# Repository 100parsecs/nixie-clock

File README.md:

# nixie-clock
This is a design for a nixie tube clock that runs exclusively on transistor logic.

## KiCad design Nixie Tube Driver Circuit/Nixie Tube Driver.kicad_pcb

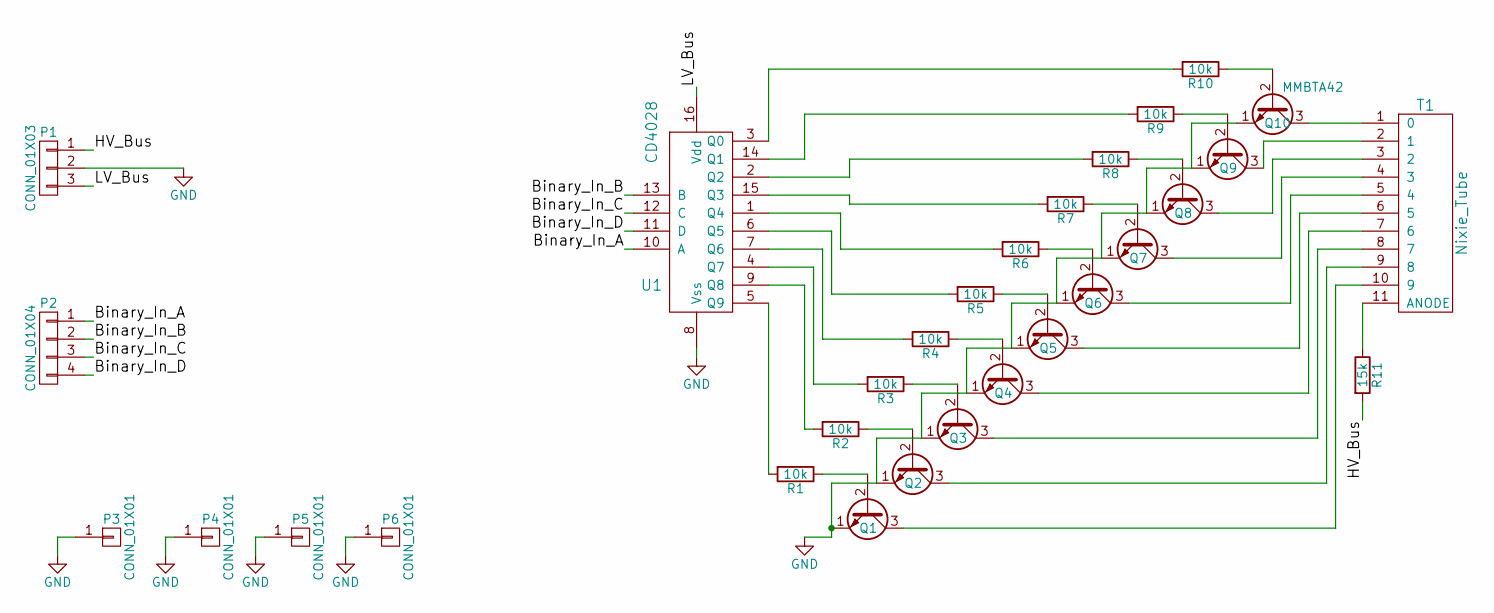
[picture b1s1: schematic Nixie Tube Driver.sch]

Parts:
P1: CONN_01X03; Molex_Microfit3_Header_02x02_Straight_43045-0428
P2: CONN_01X04; Molex_Microfit3_Header_02x02_Straight_43045-0428
P3, P4, P5, P6: CONN_01X01; MountingHole_2.5mm_Pad
Q1, Q2, Q3, Q4, Q5, Q6, Q7, Q8, Q9, Q10: MMBTA42; SOT-23_Handsoldering
R1, R2, R3, R4, R5, R6, R7, R8, R9, R10: 10k; R_0805_HandSoldering
R11: 15k; R_1218_HandSoldering
T1: Nixie_Tube; IN12B_Discrete_Pins_Keyed_Measured_Pos
U1: CD4028; SOIC-16_3.9x9.9mm_Pitch1.27mm

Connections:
/Binary_In_A: P2.1, U1.10 (A)
/Binary_In_B: P2.2, U1.13 (B)
/Binary_In_C: P2.3, U1.12 (C)
/Binary_In_D: P2.4, U1.11 (D)
/HV_Bus: P1.1, R11.2
/LV_Bus: P1.3, U1.16 (Vdd)
GND: P1.2, P3.1, P4.1, P5.1, P6.1, Q1.1 (E), Q2.1 (E), Q3.1 (E), Q4.1 (E), Q5.1 (E), Q6.1 (E), Q7.1 (E), Q8.1 (E), Q9.1 (E), Q10.1 (E), U1.8 (Vss)
unnamed: Q1.2 (B), R1.1
unnamed: Q1.3 (C), T1.10 (9)
unnamed: Q2.2 (B), R2.1
unnamed: Q2.3 (C), T1.9 (8)
unnamed: Q3.2 (B), R3.1
unnamed: Q3.3 (C), T1.8 (7)
unnamed: Q4.2 (B), R4.1
unnamed: Q4.3 (C), T1.7 (6)
unnamed: Q5.2 (B), R5.1
unnamed: Q5.3 (C), T1.6 (5)
unnamed: Q6.2 (B), R6.1
unnamed: Q6.3 (C), T1.5 (4)
unnamed: Q7.2 (B), R7.1
unnamed: Q7.3 (C), T1.4 (3)
unnamed: Q8.2 (B), R8.1
unnamed: Q8.3 (C), T1.3 (2)
unnamed: Q9.2 (B), R9.1
unnamed: Q9.3 (C), T1.2 (1)
unnamed: Q10.2 (B), R10.1
unnamed: Q10.3 (C), T1.1 (0)
unnamed: R1.2, U1.5 (Q9)
unnamed: R2.2, U1.9 (Q8)
unnamed: R3.2, U1.4 (Q7)
unnamed: R4.2, U1.7 (Q6)
unnamed: R5.2, U1.6 (Q5)
unnamed: R6.2, U1.1 (Q4)
unnamed: R7.2, U1.15 (Q3)
unnamed: R8.2, U1.2 (Q2)
unnamed: R9.2, U1.14 (Q1)
unnamed: R10.2, U1.3 (Q0)
unnamed: R11.1, T1.11 (ANODE)

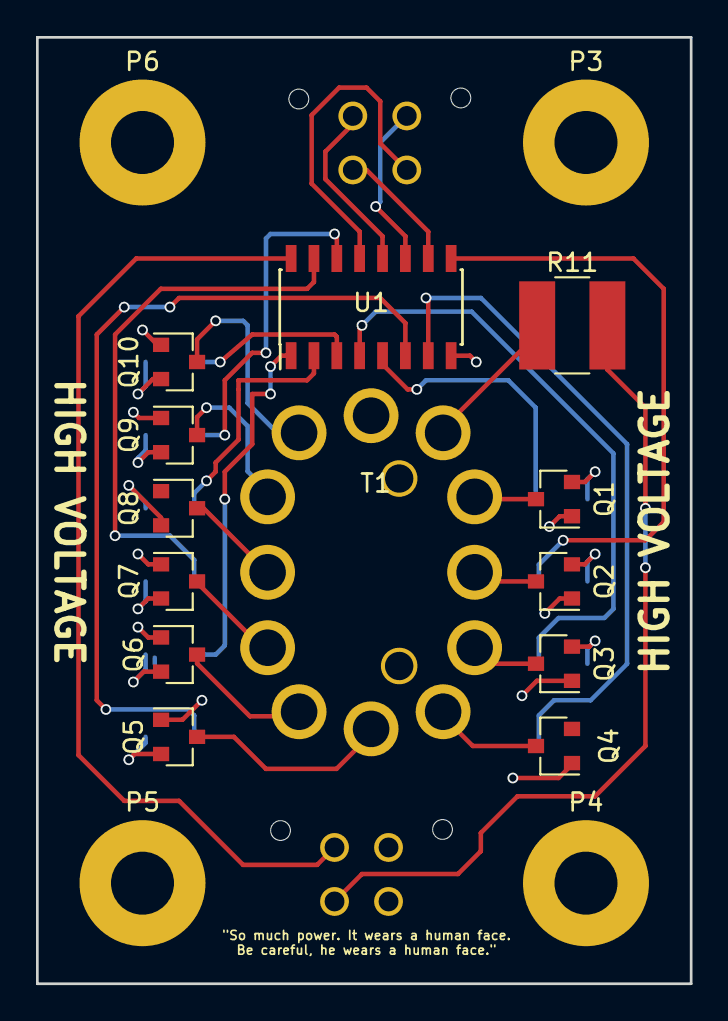
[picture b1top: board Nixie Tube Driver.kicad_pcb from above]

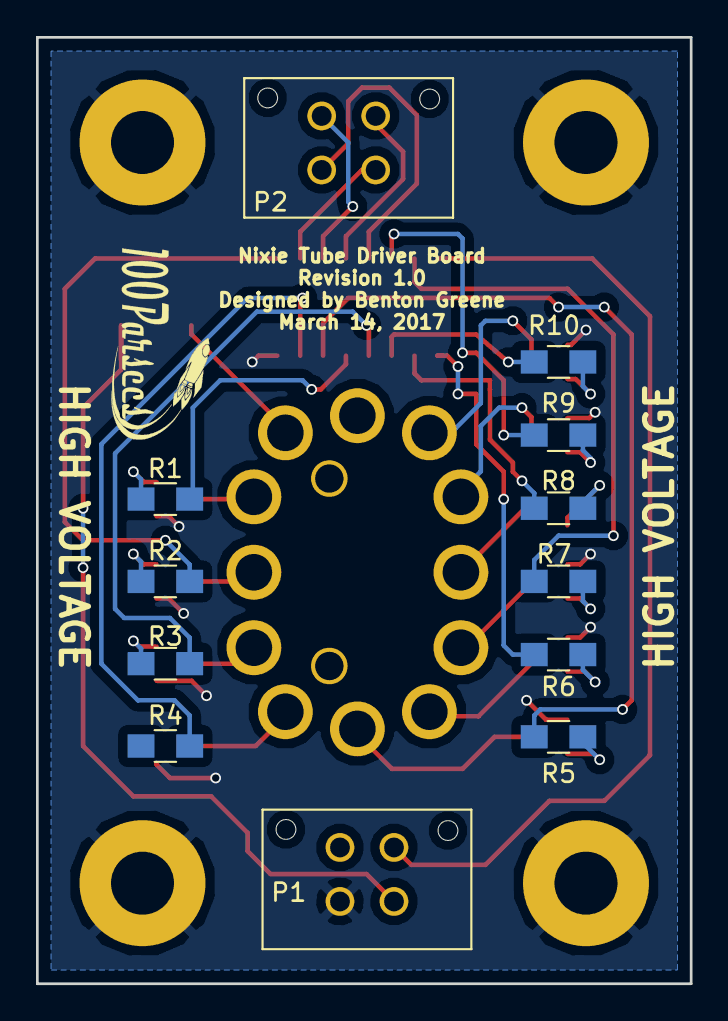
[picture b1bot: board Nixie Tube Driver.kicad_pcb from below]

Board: 2 copper layers, 36.3 x 52.6 mm, 29 parts (12 on the bottom side), 38 nets.

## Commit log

2017-03-14 Update README.md
    description of project.
2017-03-14 Add files via upload
    populating project files.
2017-03-14 Add files via upload
    custom footprint libraries for boards
2017-03-23 New method for time set button logic
    Added a new method using a quad AND gate and a quad OR gate to switch between having the time set buttons advance the display and having the clock pulses advance the time.
    Also added some extra labels for clarity
2017-03-23 Smaller board, hand solder version
    Complete rearrangement of the original board to make it smaller and added a hand solder version of the board with larger pads on the SOT23 packages.
2017-03-23 Updated Nixie footprint
    Discovered that generic IN12 measurements that I found on the internet didn't quite fit my board. "Keyed_Measured_Pos" version is custom tailored to the tube that I actually have.
2017-04-02 Fix problem with 12-hour counter logic
    Now using a NOR gate to test whether the 12-hour counter is set to zero, and using an OR gate to avoid completely suppressing the output pins of the counter.
